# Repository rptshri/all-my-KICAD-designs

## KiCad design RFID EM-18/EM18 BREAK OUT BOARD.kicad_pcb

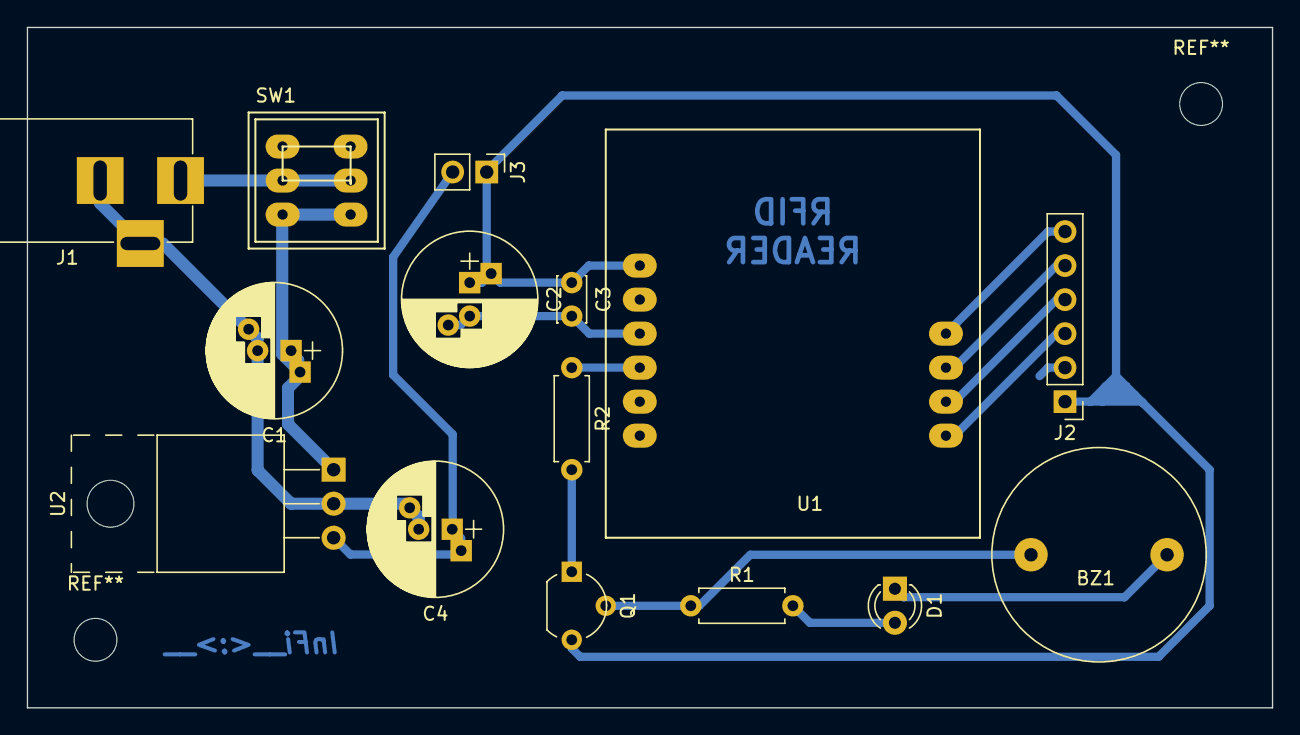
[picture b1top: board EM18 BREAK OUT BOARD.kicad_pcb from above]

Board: 2 copper layers, 93.0 x 50.8 mm, 15 parts (0 on the bottom side), 13 nets.

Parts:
BZ1: Buzzer; BUZZER
C1: 10uF; CP_Radial_D10.0mm_P2.50mm_P5.00mm
C2: 100uF; CP_Radial_D10.0mm_P2.50mm_P5.00mm
C3: 104; C_Disc_D3.4mm_W2.1mm_P2.50mm
C4: .33uF; CP_Radial_D10.0mm_P2.50mm_P5.00mm
D1: LED; LED_D3.0mm
J1: Barrel_Jack; BARREL_JACK
J2: Conn_01x06_Male; Pin_Header_Straight_1x06_Pitch2.54mm
J3: Conn_01x02; Pin_Header_Straight_1x02_Pitch2.54mm
Q1: BC557; TO-92_Molded_Wide
R1: 470; R_Axial_DIN0207_L6.3mm_D2.5mm_P7.62mm_Horizontal
R2: 2K2; R_Axial_DIN0207_L6.3mm_D2.5mm_P7.62mm_Horizontal
SW1: latchswitch; LATCH_SW
U1: EM18
U2: L7805; TO-220-3_Horizontal_Reversed

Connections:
GND: BZ1.1, C1.2, C2.2, C3.2, C4.2, D1.1, J1.2, J1.3, J2.2, U1.2, U2.2
unnamed: BZ1.2, Q1.2, R1.1
unnamed: C4.1, J3.2, U2.3
unnamed: D1.2, R1.2
unnamed: J1.1, SW1.2, SW1.5
unnamed: J2.3, U1.6
unnamed: J2.4, U1.7
unnamed: J2.5, U1.8
unnamed: J2.6, U1.9
unnamed: Q1.1, R2.2
unnamed: R2.1, U1.3
VCC: C2.1, C3.1, J2.1, J3.1, Q1.3, U1.1
VCOM: C1.1, SW1.1, SW1.4, U2.1

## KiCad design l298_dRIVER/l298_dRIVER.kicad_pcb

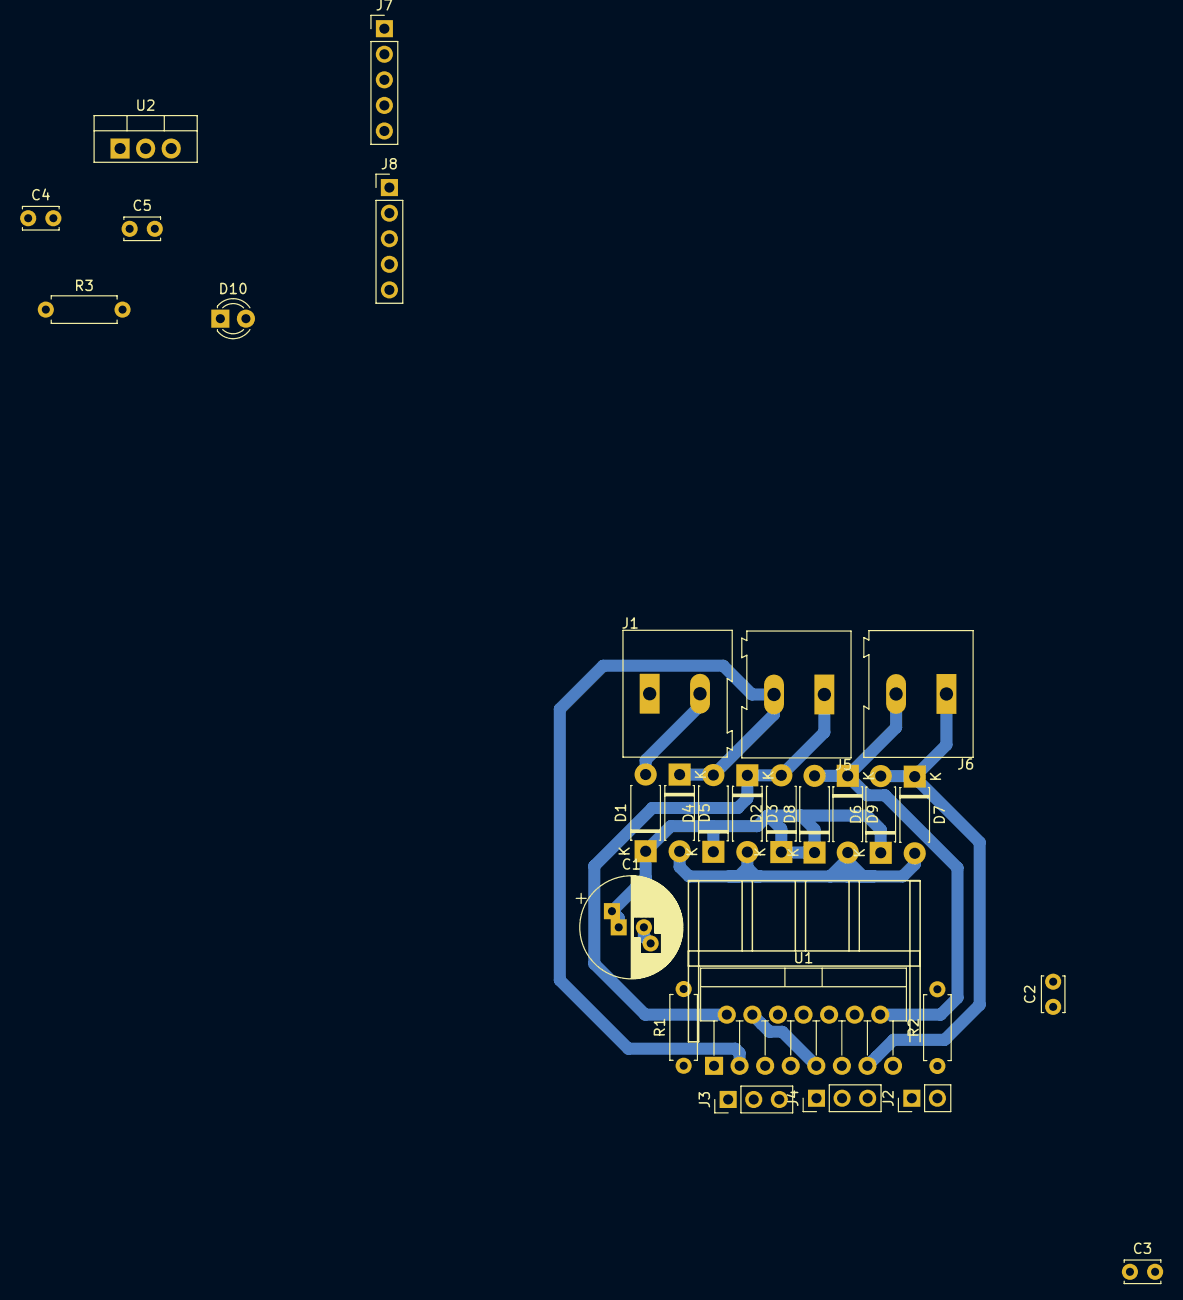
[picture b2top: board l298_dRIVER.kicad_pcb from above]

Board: 2 copper layers, 32 parts (0 on the bottom side), 17 nets.

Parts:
C1: CP1; CP_Radial_D10.0mm_P2.50mm_P5.00mm
C2: 470uF; C_Disc_D3.4mm_W2.1mm_P2.50mm
C3: 100nF; C_Disc_D3.4mm_W2.1mm_P2.50mm
C4: .33uF; C_Disc_D3.4mm_W2.1mm_P2.50mm
C5: .1uF; C_Disc_D3.4mm_W2.1mm_P2.50mm
D1, D2, D3, D4, D5, D6, D7, D8, D9: 1N4001; D_DO-41_SOD81_P7.62mm_Horizontal
D10: LED; LED_D3.0mm
H1, H2, H3, H4: MountingHole; MountingHole_3.2mm_M3_DIN965
J1, J5, J6: Screw_Terminal_01x02; TerminalBlock_Altech_AK300-2_P5.00mm
J2: Current_Sense; PinHeader_1x02_P2.54mm_Vertical
J3: Signal A; PinHeader_1x03_P2.54mm_Vertical
J4: Signal B; PinHeader_1x03_P2.54mm_Vertical
J7: +5V; PinHeader_1x05_P2.54mm_Vertical
J8: gnd; PinHeader_1x05_P2.54mm_Vertical
R1, R2, R3: R_Small; R_Axial_DIN0207_L6.3mm_D2.5mm_P7.62mm_Horizontal
U1: L298HN; TO-220-15_P2.54x2.54mm_StaggerOdd_Lead4.58mm_Vertical_with_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
U2: L7805; TO-220-3_Vertical

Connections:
+5V: C5.1, J7.1, J7.2, J7.3, J7.4, J7.5, R3.1, U2.3
/S1: J2.1, R1.1, U1.1
/S2: J2.2, R2.1, U1.15
GND: C1.2, C2.2, C3.2, C4.2, C5.2, D3.2, D5.2, D7.2, D9.2, D10.1, J1.1, J8.1, J8.2, J8.3, J8.4, J8.5, R1.2, R2.2, U1.8, U2.2
unnamed: D2.2, D3.1, J5.1, U1.2
unnamed: D4.2, D5.1, J5.2, U1.3
unnamed: D6.2, D7.1, J6.1, U1.13
unnamed: D8.2, D9.1, J6.2, U1.14
unnamed: D10.2, R3.2
unnamed: J3.1, U1.5
unnamed: J3.2, U1.7
unnamed: J3.3, U1.6
unnamed: J4.1, U1.10
unnamed: J4.2, U1.12
unnamed: J4.3, U1.11
VCC: C1.1, C2.1, C3.1, C4.1, D1.1, D2.1, D4.1, D6.1, D8.1, U1.4, U1.9, U2.1
VDC: D1.2, J1.2

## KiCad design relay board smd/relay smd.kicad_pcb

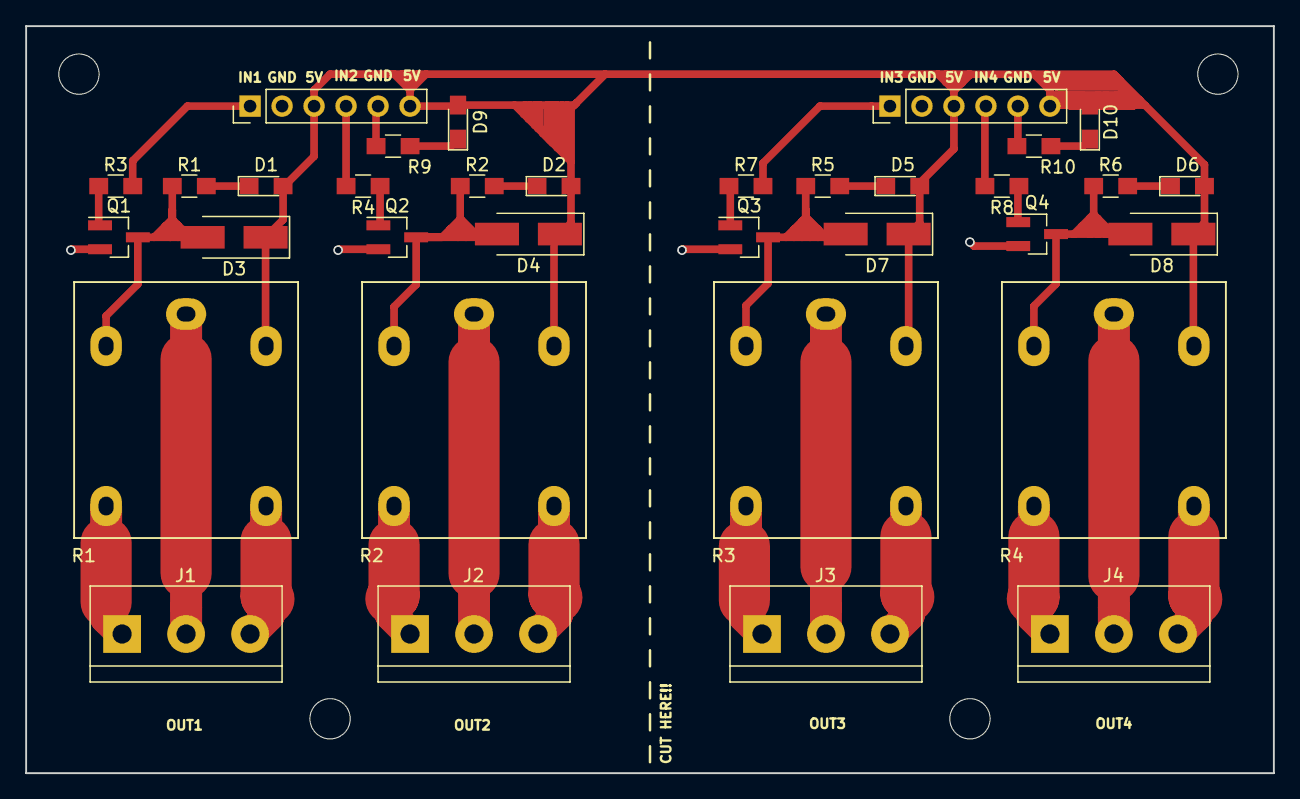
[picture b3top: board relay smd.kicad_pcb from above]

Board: 2 copper layers, 99.1 x 59.3 mm, 34 parts (0 on the bottom side), 32 nets.

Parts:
D1, D2, D5, D6, D9, D10: LED; LED_0805_HandSoldering
D3, D4, D7, D8: 1n4007; D_SMA_Handsoldering
J1, J2, J3, J4: Screw_Terminal_01x03; TerminalBlock_bornier-3_P5.08mm
J1#2, J4#2: Conn_01x06; Pin_Header_Straight_1x06_Pitch2.54mm
Q1, Q2, Q3, Q4: BC847; SOT-23_Handsoldering
R1, R2, R5, R6: 330; R_0805_HandSoldering
R1#2, R2#2, R3#2, R4#2: G5Q-1; RELAY
R3, R4, R7, R8: 2.2k; R_0805_HandSoldering
R9, R10: 500; R_0805_HandSoldering

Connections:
+5V: D1.2, D2.2, D3.1, D4.1, D5.2, D6.2, D7.1, D8.1, D9.2, D10.2, J1#2.3, J1#2.6, J4#2.3, J4#2.6, R1#2.5, R2#2.5, R3#2.5, R4#2.5
/p1: J1#2.1, R3.2
/p2: J1#2.4, R4.2
/p3: J4#2.1, R7.2
/p4: J4#2.4, R8.2
GND: J1#2.2, J1#2.5, J4#2.2, J4#2.5, Q1.2, Q2.2, Q3.2, Q4.2, R9.1, R10.1
unnamed: D1.1, R1.2
unnamed: D2.1, R2.2
unnamed: D3.2, Q1.3, R1.1, R1#2.1
unnamed: D4.2, Q2.3, R2.1, R2#2.1
unnamed: D5.1, R5.2
unnamed: D6.1, R6.2
unnamed: D7.2, Q3.3, R3#2.1, R5.1
unnamed: D8.2, Q4.3, R4#2.1, R6.1
unnamed: D9.1, R9.2
unnamed: D10.1, R10.2
unnamed: J1.1, R1#2.4
unnamed: J1.2, R1#2.2
unnamed: J1.3, R1#2.3
unnamed: J2.1, R2#2.4
unnamed: J2.2, R2#2.2
unnamed: J2.3, R2#2.3
unnamed: J3.1, R3#2.4
unnamed: J3.2, R3#2.2
unnamed: J3.3, R3#2.3
unnamed: J4.1, R4#2.4
unnamed: J4.2, R4#2.2
unnamed: J4.3, R4#2.3
unnamed: Q1.1, R3.1
unnamed: Q2.1, R4.1
unnamed: Q3.1, R7.1
unnamed: Q4.1, R8.1

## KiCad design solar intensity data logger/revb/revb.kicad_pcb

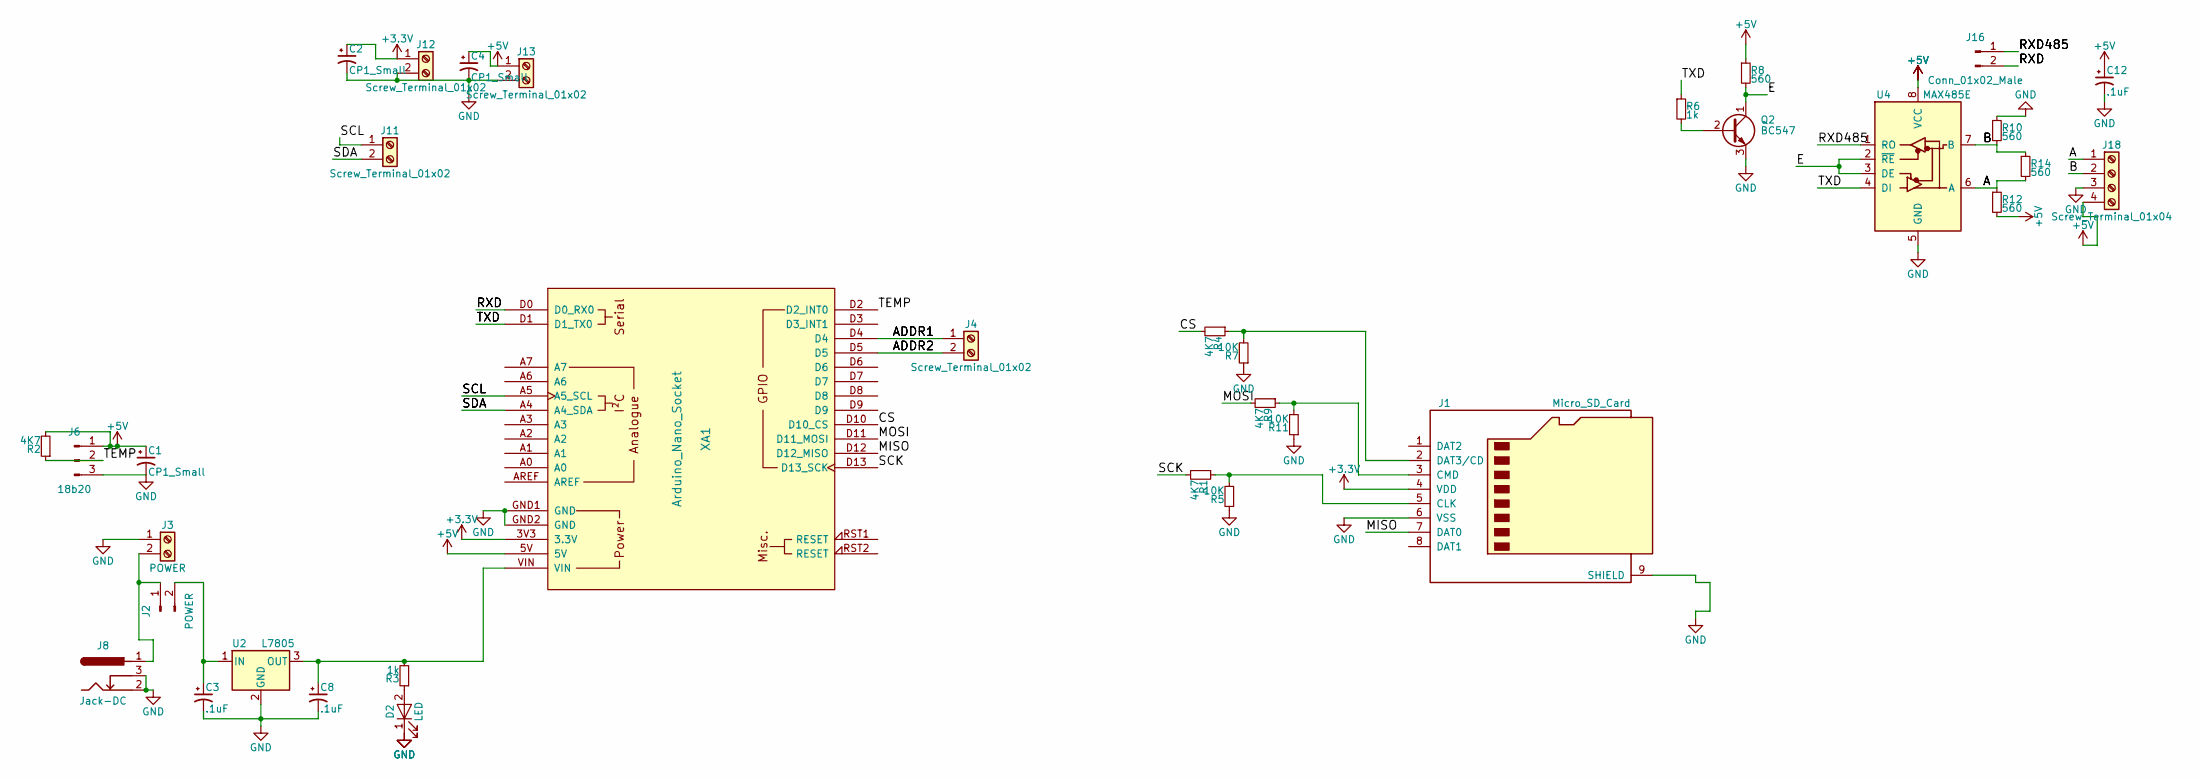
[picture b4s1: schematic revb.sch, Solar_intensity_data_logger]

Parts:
C1, C2, C4: CP1_Small; CP_Radial_D4.0mm_P1.50mm
C3, C8, C12: .1uF; CP_Radial_D4.0mm_P1.50mm
D2: LED; LED_D5.0mm
J1: Micro_SD_Card; MicroSd_Wurth_693072010801
J2: POWER; Pin_Header_Straight_1x02_Pitch2.54mm
J3: POWER; TerminalBlock_bornier-2_P5.08mm
J4, J11, J12, J13: Screw_Terminal_01x02; TerminalBlock_bornier-2_P5.08mm
J6: 18b20; Pin_Header_Straight_1x03_Pitch2.54mm
J8: Jack-DC; BARREL_JACK
J16: Conn_01x02_Male; Pin_Header_Straight_1x02_Pitch2.54mm
J18: Screw_Terminal_01x04; TerminalBlock_Altech_AK300-4_P5.00mm
Q2: BC547; TO-92_Molded_Wide
R1: 4K7; R_Axial_DIN0207_L6.3mm_D2.5mm_P7.62mm_Horizontal
R2, R4, R9: 4K7; R_0805_HandSoldering
R3, R6: 1k; R_0805_HandSoldering
R5: 10K; R_0805_HandSoldering
R7, R11: 10K; R_Axial_DIN0207_L6.3mm_D2.5mm_P7.62mm_Horizontal
R8, R14: 560; R_0805_HandSoldering
R10, R12: 560; R_Axial_DIN0207_L6.3mm_D2.5mm_P7.62mm_Horizontal
U2: L7805; TO-220-3_Vertical
U4: MAX485E; DIP-8_W7.62mm_LongPads
XA1: Arduino_Nano_Socket

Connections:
+3V3: C2.1, J1.4 (VDD), J12.1, XA1.3V3 (3.3V)
+5V: C1.1, C4.1, C12.1, J6.1, J13.1, J18.4, R2.2, R8.1, R12.2, U4.8 (VCC), XA1.5V
/A: J18.1, R12.1, R14.2, U4.6 (A)
/ADDR1: J4.1, XA1.D4
/ADDR2: J4.2, XA1.D5
/B: J18.2, R10.2, R14.1, U4.7 (B)
/CS: R4.2, XA1.D10 (D10_CS)
/E: Q2.1 (C), R8.2, U4.2 (~RE), U4.3 (DE)
/MISO: J1.7 (DAT0), XA1.D12 (D12_MISO)
/MOSI: R9.2, XA1.D11 (D11_MOSI)
/RXD: J16.2, XA1.D0 (D0_RX0)
/RXD485: J16.1, U4.1 (RO)
/SCK: R1.2, XA1.D13 (D13_SCK)
/SCL: J11.1, XA1.A5 (A5_SCL)
/SDA: J11.2, XA1.A4 (A4_SDA)
/TEMP: J6.2, R2.1, XA1.D2 (D2_INT0)
/TXD: R6.1, U4.4 (DI), XA1.D1 (D1_TX0)
GND: C1.2, C2.2, C3.2, C4.2, C8.2, C12.2, D2.1 (K), J1.6 (VSS), J1.9 (SHIELD), J3.1, J6.3, J8.2, J8.3, J12.2, J13.2, J18.3, Q2.3 (E), R5.1, R7.1, R10.1, R11.1, U2.2 (GND), U4.5 (GND), XA1.GND1 (GND), XA1.GND2 (GND)
unnamed: C3.1, J2.2, U2.1 (IN)
unnamed: C8.1, R3.2, U2.3 (OUT), XA1.VIN
unnamed: D2.2 (A), R3.1
unnamed: J1.2 (DAT3/CD), R4.1, R7.2
unnamed: J1.3 (CMD), R9.1, R11.2
unnamed: J1.5 (CLK), R1.1, R5.2
unnamed: J2.1, J3.2, J8.1
unnamed: Q2.2 (B), R6.2

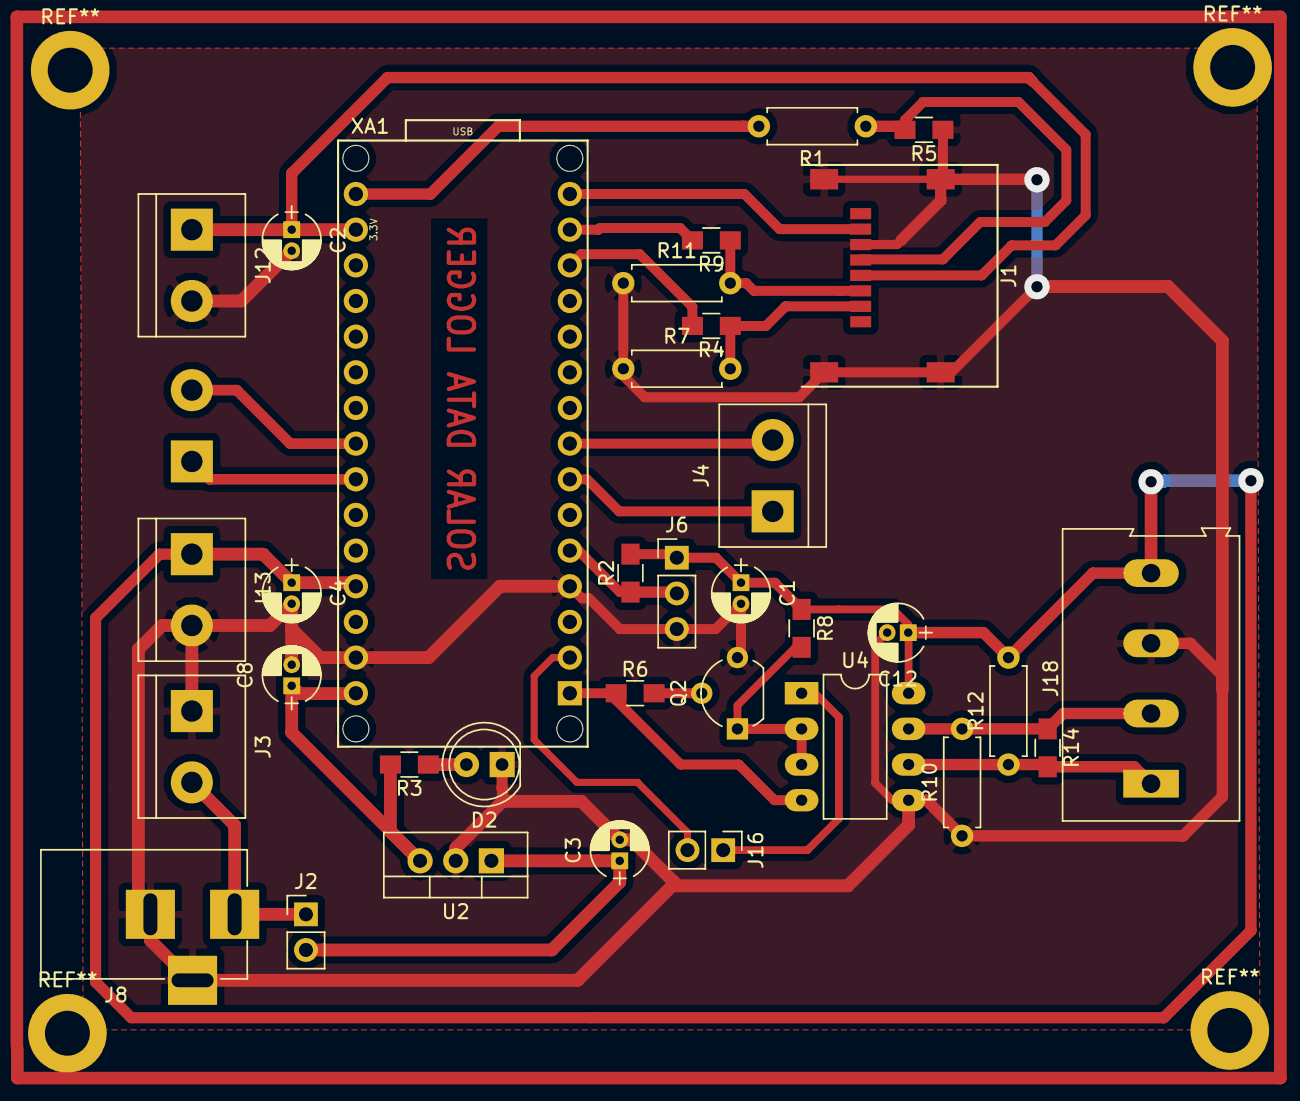
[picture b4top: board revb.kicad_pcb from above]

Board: 2 copper layers, 35 parts (1 on the bottom side), 26 nets.

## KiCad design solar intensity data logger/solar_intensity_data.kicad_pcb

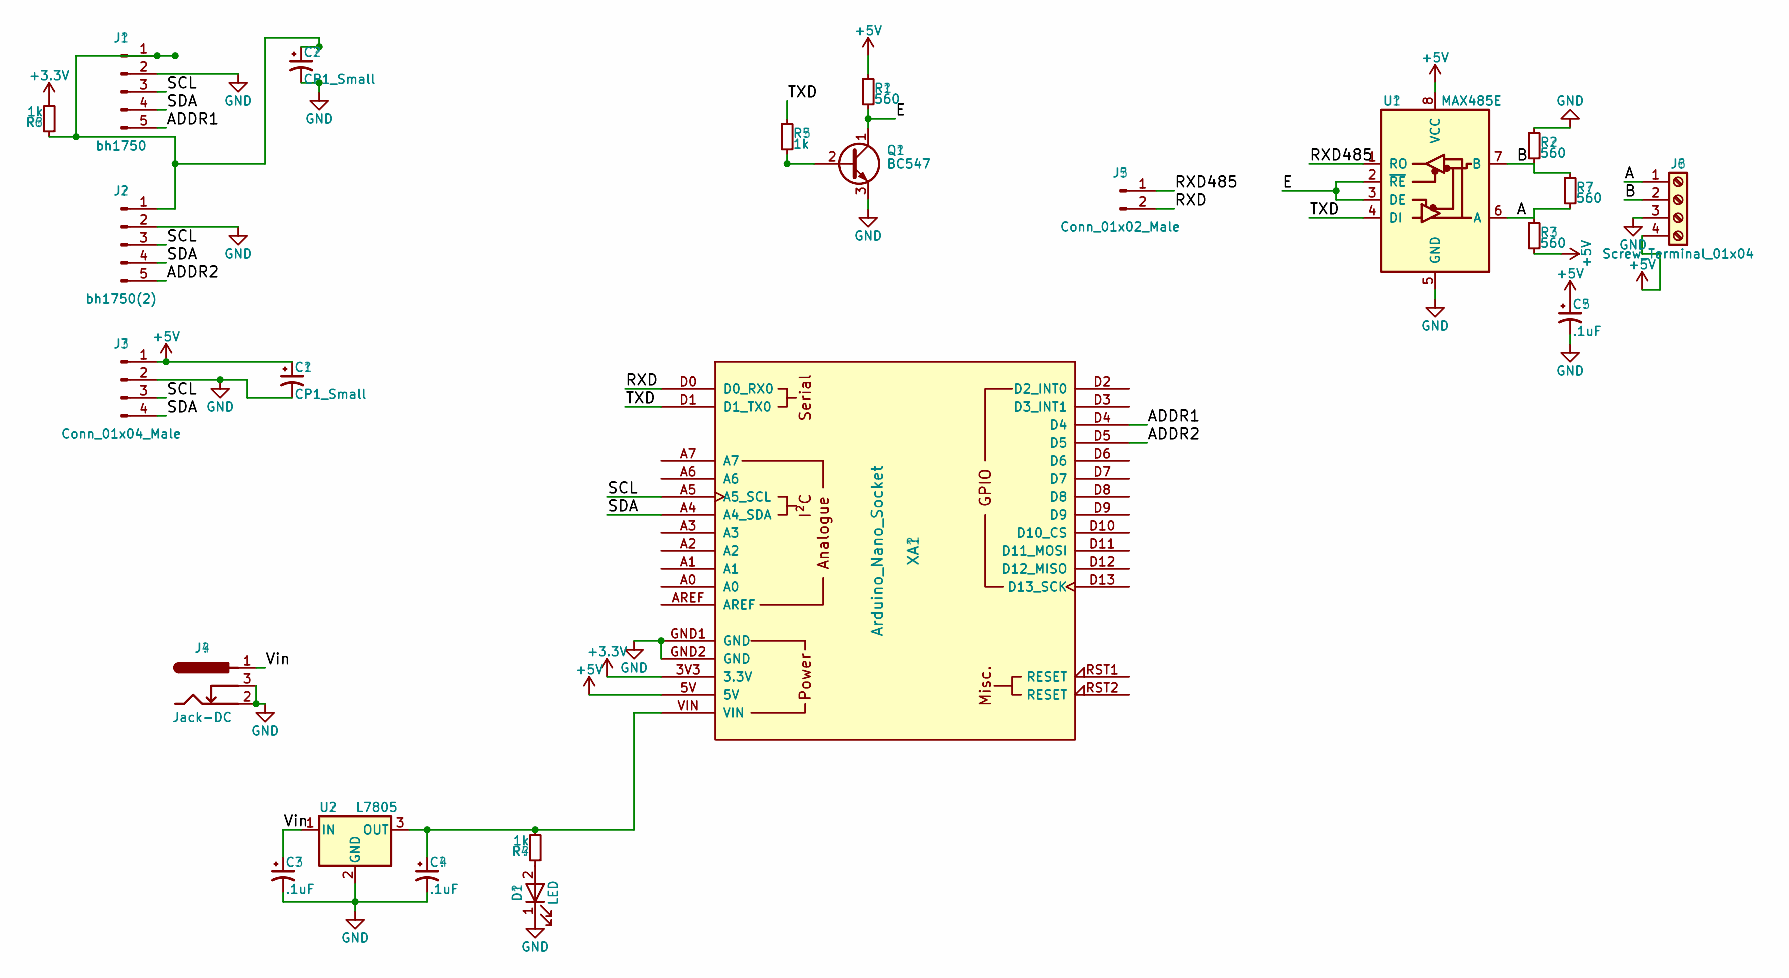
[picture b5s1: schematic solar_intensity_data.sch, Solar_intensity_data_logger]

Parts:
C1, C2: CP1_Small; CP_Radial_D10.0mm_P5.00mm_P7.50mm
C3, C4, C5: .1uF; CP_Radial_D10.0mm_P5.00mm_P7.50mm
D1: LED; LED_D5.0mm
J1: bh1750; Pin_Header_Straight_1x05_Pitch2.54mm
J2: bh1750(2); Pin_Header_Straight_1x05_Pitch2.54mm
J3: Conn_01x04_Male; Pin_Header_Straight_1x04_Pitch2.54mm
J4: Jack-DC; BARREL_JACK
J5: Conn_01x02_Male; Pin_Header_Straight_1x02_Pitch2.54mm
J6: Screw_Terminal_01x04; TerminalBlock_Altech_AK300-4_P5.00mm
Q1: BC547; TO-92_Molded_Wide
R1, R2, R3, R7: 560; R_Axial_DIN0207_L6.3mm_D2.5mm_P7.62mm_Horizontal
R4, R5, R6: 1k; R_Axial_DIN0207_L6.3mm_D2.5mm_P7.62mm_Horizontal
U1: MAX485E; DIP-8_W7.62mm_LongPads
U2: L7805; TO-220-3_Vertical
XA1: Arduino_Nano_Socket

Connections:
+3V3: R6.2, XA1.3V3 (3.3V)
+5V: C1.1, C5.1, J3.1, J6.4, R1.1, R3.2, U1.8 (VCC), XA1.5V
/A: J6.1, R3.1, R7.2, U1.6 (A)
/ADDR1: J1.5, XA1.D4
/ADDR2: J2.5, XA1.D5
/B: J6.2, R2.2, R7.1, U1.7 (B)
/E: Q1.1 (C), R1.2, U1.2 (~RE), U1.3 (DE)
/RXD: J5.2, XA1.D0 (D0_RX0)
/RXD485: J5.1, U1.1 (RO)
/SCL: J1.3, J2.3, J3.3, XA1.A5 (A5_SCL)
/SDA: J1.4, J2.4, J3.4, XA1.A4 (A4_SDA)
/TXD: R5.1, U1.4 (DI), XA1.D1 (D1_TX0)
/Vin: C3.1, J4.1, U2.1 (IN)
GND: C1.2, C2.2, C3.2, C4.2, C5.2, D1.1 (K), J1.2, J2.2, J3.2, J4.2, J4.3, J6.3, Q1.3 (E), R2.1, U1.5 (GND), U2.2 (GND), XA1.GND1 (GND), XA1.GND2 (GND)
unnamed: C2.1, J1.1, J2.1, R6.1
unnamed: C4.1, R4.2, U2.3 (OUT), XA1.VIN
unnamed: D1.2 (A), R4.1
unnamed: Q1.2 (B), R5.2

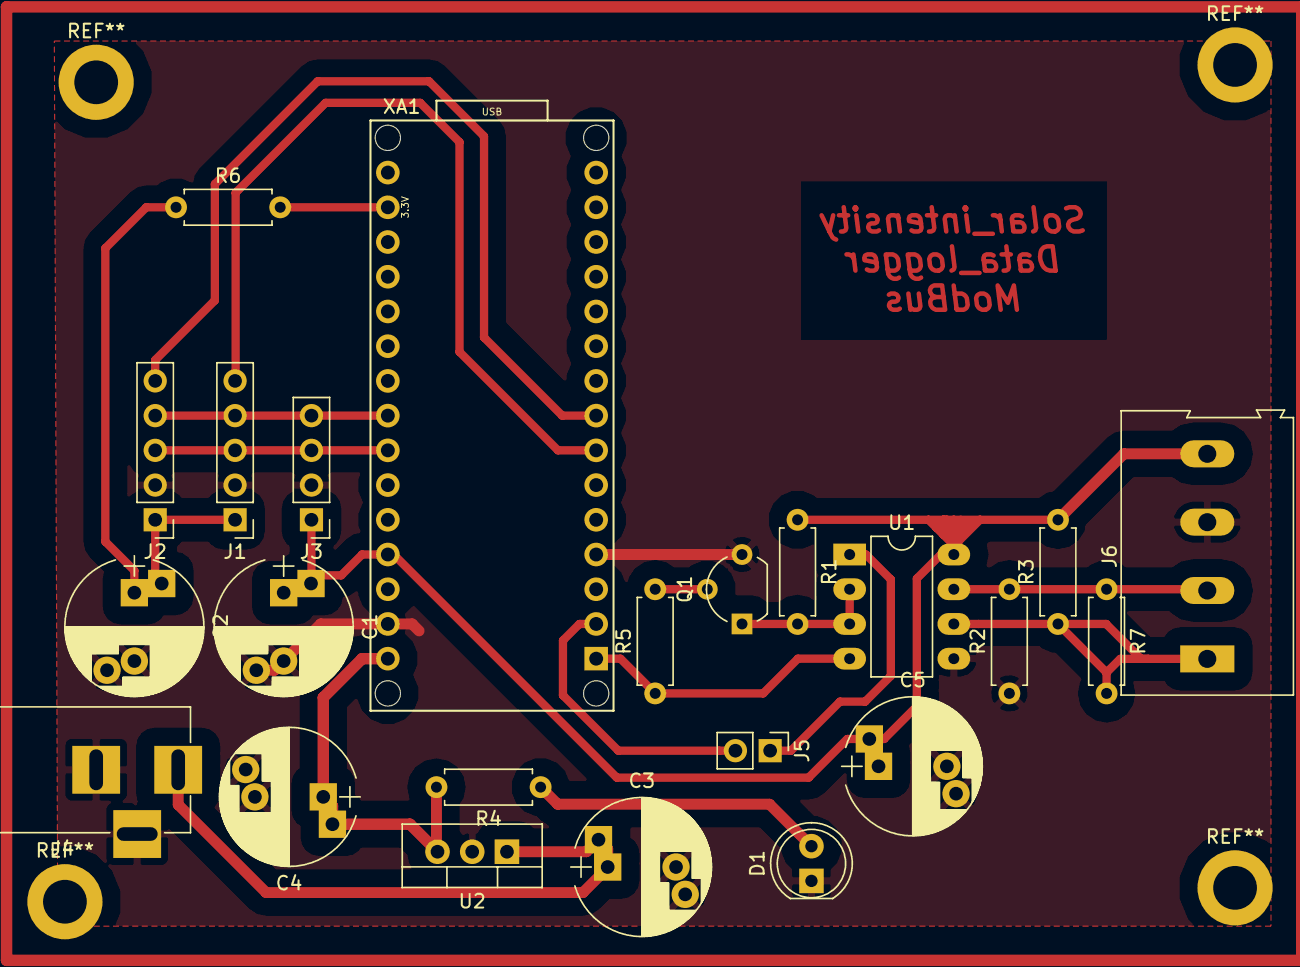
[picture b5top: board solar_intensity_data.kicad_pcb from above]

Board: 2 copper layers, 23 parts (0 on the bottom side), 18 nets.

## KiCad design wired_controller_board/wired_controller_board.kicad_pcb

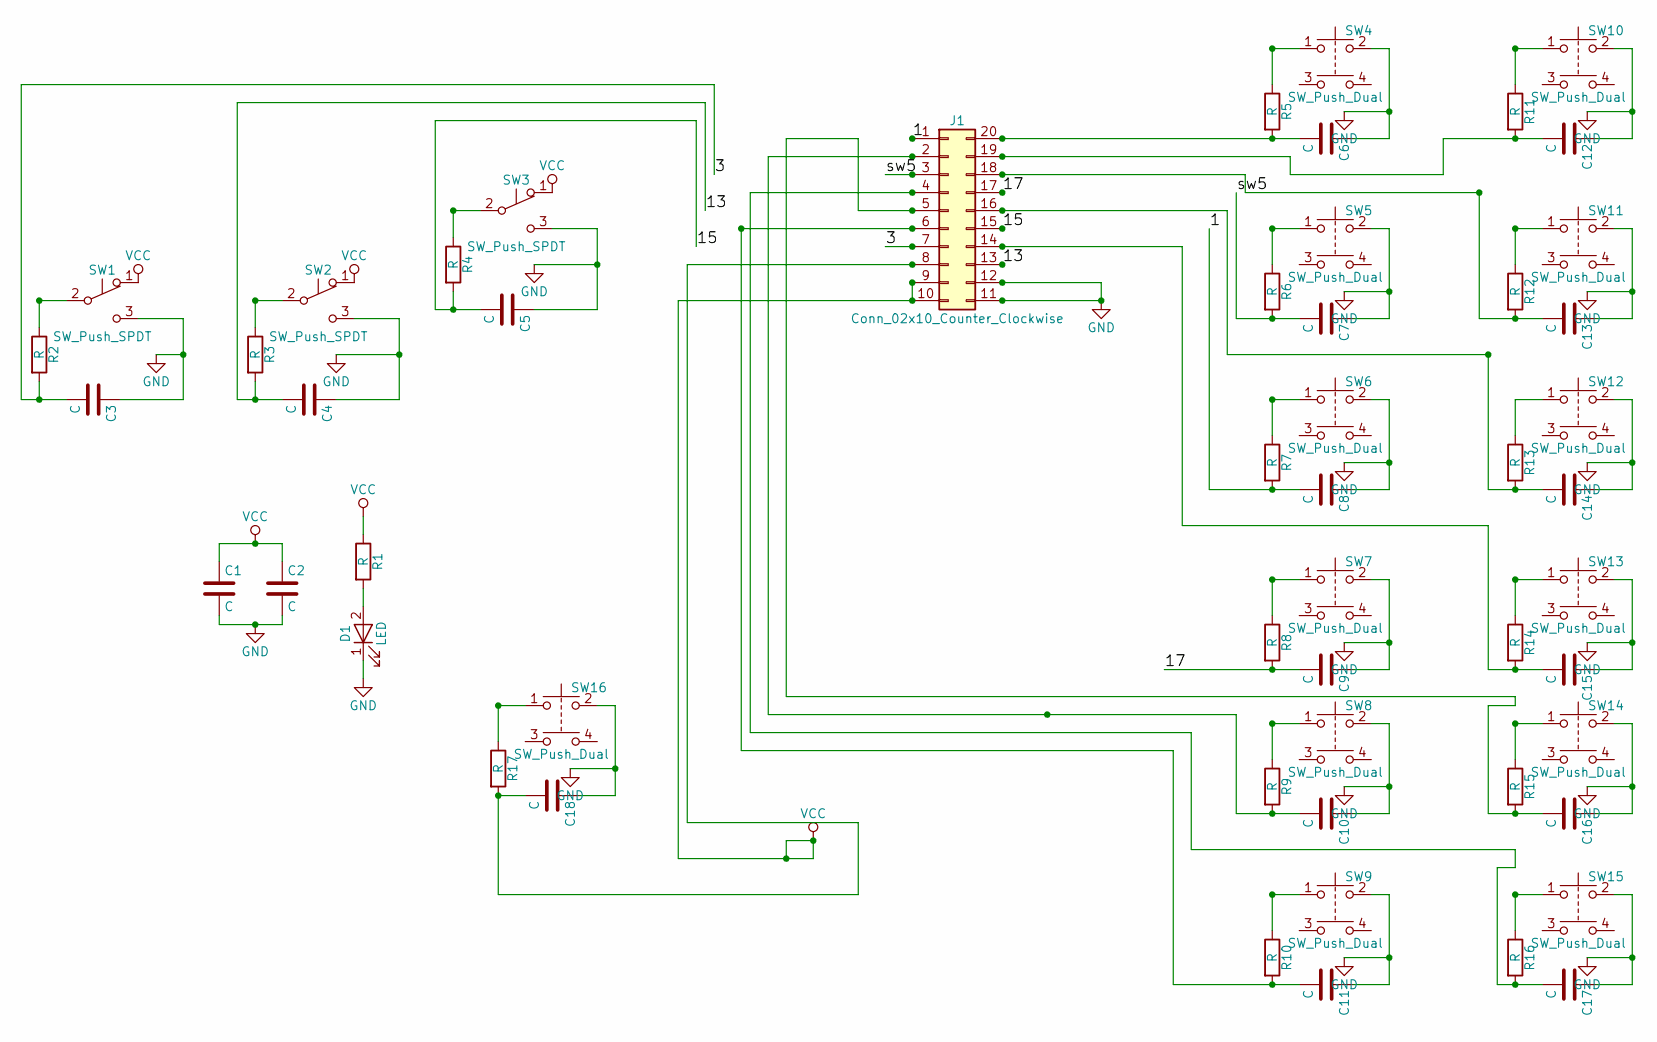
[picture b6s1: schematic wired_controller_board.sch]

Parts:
C1, C2, C3, C4, C5, C6, C7, C8, C9, C10, C11, C12, C13, C14, C15, C16, C17, C18: C; C_Disc_D3.4mm_W2.1mm_P2.50mm
D1: LED; LED_D3.0mm
J1: Conn_02x10_Counter_Clockwise; Pin_Header_Angled_2x10_Pitch2.54mm
R1, R2, R3, R4, R5, R6, R7, R8, R9, R10, R11, R12, R13, R14, R15, R16, R17: R; R_Axial_DIN0207_L6.3mm_D2.5mm_P7.62mm_Horizontal
SW1, SW2, SW3: SW_Push_SPDT; SW_CuK_OS102011MA1QN1_SPDT_Angled
SW4, SW5, SW6, SW7, SW8, SW9, SW10, SW11, SW12, SW13, SW14, SW15, SW16: SW_Push_Dual; SW_PUSH_6mm

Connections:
/1: C8.2, J1.1, R7.2
/3: C3.2, J1.7, R2.2
/13: C4.2, J1.13, R3.2
/15: C5.2, J1.15, R4.2
/17: C9.2, J1.17, R8.2
/sw5: C7.2, J1.3, R6.2
GND: C1.2, C2.2, C3.1, C4.1, C5.1, C6.1, C7.1, C8.1, C9.1, C10.1, C11.1, C12.1, C13.1, C14.1, C15.1, C16.1, C17.1, C18.1, D1.1 (K), J1.11, J1.12, SW1.3 (C), SW2.3 (C), SW3.3 (C), SW4.2, SW5.2, SW6.2, SW7.2, SW8.2, SW9.2, SW10.2, SW11.2, SW12.2, SW13.2, SW14.2, SW15.2, SW16.2
unnamed: C6.2, J1.20, R5.2
unnamed: C10.2, J1.2, R9.2
unnamed: C11.2, J1.6, R10.2
unnamed: C12.2, J1.19, R11.2
unnamed: C13.2, J1.18, R12.2
unnamed: C14.2, J1.16, R13.2
unnamed: C15.2, J1.14, R14.2
unnamed: C16.2, J1.5, R15.2
unnamed: C17.2, J1.4, R16.2
unnamed: C18.2, J1.8, R17.2
unnamed: D1.2 (A), R1.2
unnamed: R2.1, SW1.2 (B)
unnamed: R3.1, SW2.2 (B)
unnamed: R4.1, SW3.2 (B)
unnamed: R5.1, SW4.1
unnamed: R6.1, SW5.1
unnamed: R7.1, SW6.1
unnamed: R8.1, SW7.1
unnamed: R9.1, SW8.1
unnamed: R10.1, SW9.1
unnamed: R11.1, SW10.1
unnamed: R12.1, SW11.1
unnamed: R13.1, SW12.1
unnamed: R14.1, SW13.1
unnamed: R15.1, SW14.1
unnamed: R16.1, SW15.1
unnamed: R17.1, SW16.1
VCC: C1.1, C2.1, J1.9, J1.10, R1.1, SW1.1 (A), SW2.1 (A), SW3.1 (A)

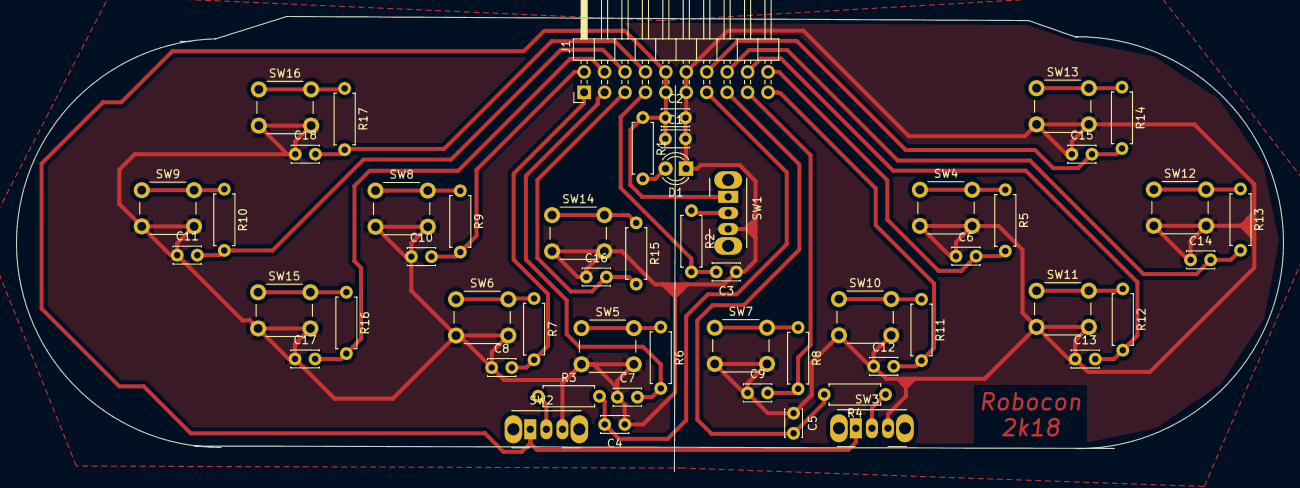
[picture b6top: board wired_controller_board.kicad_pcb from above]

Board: 2 copper layers, 157.5 x 56.6 mm, 53 parts (0 on the bottom side), 35 nets.
